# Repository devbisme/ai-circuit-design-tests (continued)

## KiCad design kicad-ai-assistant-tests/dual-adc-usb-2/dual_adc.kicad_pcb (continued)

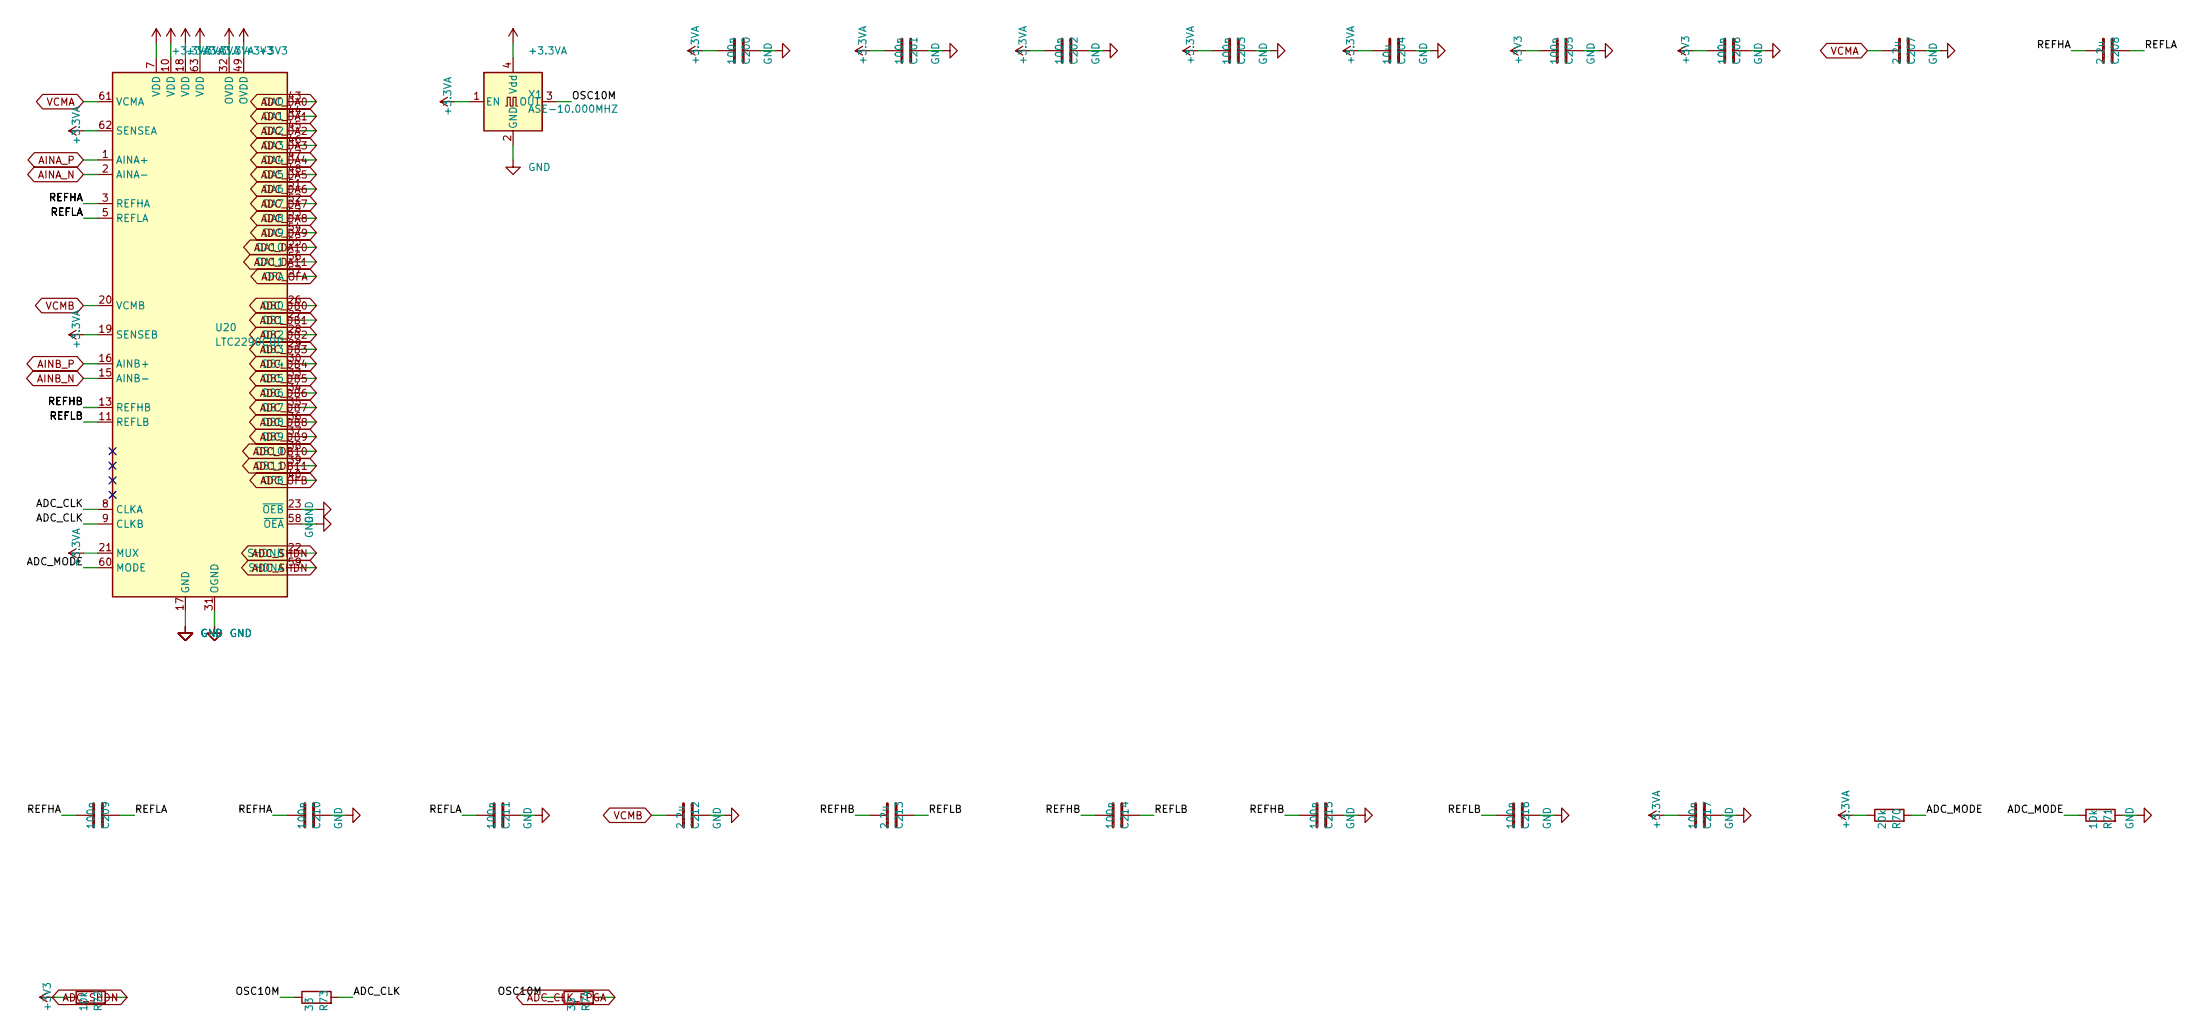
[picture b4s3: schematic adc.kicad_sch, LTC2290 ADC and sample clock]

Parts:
C200, C201, C202, C203, C205, C206, C209, C210, C211, C214, C215, C216, C217: 100n; C_0603_1608Metric
C204: 10u; C_0805_2012Metric
C207, C208, C212, C213: 2.2u; C_0603_1608Metric
R70: 20k; R_0603_1608Metric
R71, R72: 10k; R_0603_1608Metric
R73, R74: 33; R_0603_1608Metric
U20: LTC2290CUP; QFN-64-1EP_9x9mm_P0.5mm_EP7.15x7.15mm
X1: ASE-10.000MHZ; Oscillator_SMD_Abracon_ASE-4Pin_3.2x2.5mm

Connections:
+3.3VA: C200.1, C201.1, C202.1, C203.1, C204.1, C217.1, R70.1, U20.7 (VDD), U20.10 (VDD), U20.18 (VDD), U20.19 (SENSEB), U20.21 (MUX), U20.62 (SENSEA), U20.63 (VDD), X1.1 (EN), X1.4 (Vdd); also elsewhere on the board
+3V3: C205.1, C206.1, R72.1, U20.32 (OVDD), U20.49 (OVDD); also elsewhere on the board
/LTC2290 ADC and sample clock/ADC_CLK: R73.2, U20.8 (CLKA), U20.9 (CLKB)
/LTC2290 ADC and sample clock/ADC_MODE: R70.2, R71.1, U20.60 (MODE)
/LTC2290 ADC and sample clock/OSC10M: R73.1, R74.1, X1.3 (OUT)
/LTC2290 ADC and sample clock/REFHA: C208.1, C209.1, C210.1, U20.3 (REFHA), U20.4 (REFHA)
/LTC2290 ADC and sample clock/REFHB: C213.1, C214.1, C215.1, U20.13 (REFHB), U20.14 (REFHB)
/LTC2290 ADC and sample clock/REFLA: C208.2, C209.2, C211.1, U20.5 (REFLA), U20.6 (REFLA)
/LTC2290 ADC and sample clock/REFLB: C213.2, C214.2, C216.1, U20.11 (REFLB), U20.12 (REFLB)
ADC_CLK_FPGA: R74.2; also elsewhere on the board
ADC_DA0: U20.43 (DA0); also elsewhere on the board
ADC_DA1: U20.44 (DA1); also elsewhere on the board
ADC_DA2: U20.45 (DA2); also elsewhere on the board
ADC_DA3: U20.46 (DA3); also elsewhere on the board
ADC_DA4: U20.47 (DA4); also elsewhere on the board
ADC_DA5: U20.48 (DA5); also elsewhere on the board
ADC_DA6: U20.51 (DA6); also elsewhere on the board
ADC_DA7: U20.52 (DA7); also elsewhere on the board
ADC_DA8: U20.53 (DA8); also elsewhere on the board
ADC_DA9: U20.54 (DA9); also elsewhere on the board
ADC_DA10: U20.55 (DA10); also elsewhere on the board
ADC_DA11: U20.56 (DA11); also elsewhere on the board
ADC_DB0: U20.26 (DB0); also elsewhere on the board
ADC_DB1: U20.27 (DB1); also elsewhere on the board
ADC_DB2: U20.28 (DB2); also elsewhere on the board
ADC_DB3: U20.29 (DB3); also elsewhere on the board
ADC_DB4: U20.30 (DB4); also elsewhere on the board
ADC_DB5: U20.33 (DB5); also elsewhere on the board
ADC_DB6: U20.34 (DB6); also elsewhere on the board
ADC_DB7: U20.35 (DB7); also elsewhere on the board
ADC_DB8: U20.36 (DB8); also elsewhere on the board
ADC_DB9: U20.37 (DB9); also elsewhere on the board
ADC_DB10: U20.38 (DB10); also elsewhere on the board
ADC_DB11: U20.39 (DB11); also elsewhere on the board
ADC_OFA: U20.57 (OFA); also elsewhere on the board
ADC_OFB: U20.40 (OFB); also elsewhere on the board
ADC_SHDN: R72.2, U20.22 (SHDNB), U20.59 (SHDNA); also elsewhere on the board
AINA_N: U20.2 (AINA-); also elsewhere on the board
AINA_P: U20.1 (AINA+); also elsewhere on the board
AINB_N: U20.15 (AINB-); also elsewhere on the board
AINB_P: U20.16 (AINB+); also elsewhere on the board
GND: C200.2, C201.2, C202.2, C203.2, C204.2, C205.2, C206.2, C207.2, C210.2, C211.2, C212.2, C215.2, C216.2, C217.2, R71.2, U20.17 (GND), U20.23 (~OEB), U20.31 (OGND), U20.50 (OGND), U20.58 (~OEA), U20.64 (GND), U20.65 (GND), X1.2 (GND); also elsewhere on the board
VCMA: C207.1, U20.61 (VCMA); also elsewhere on the board
VCMB: C212.1, U20.20 (VCMB); also elsewhere on the board

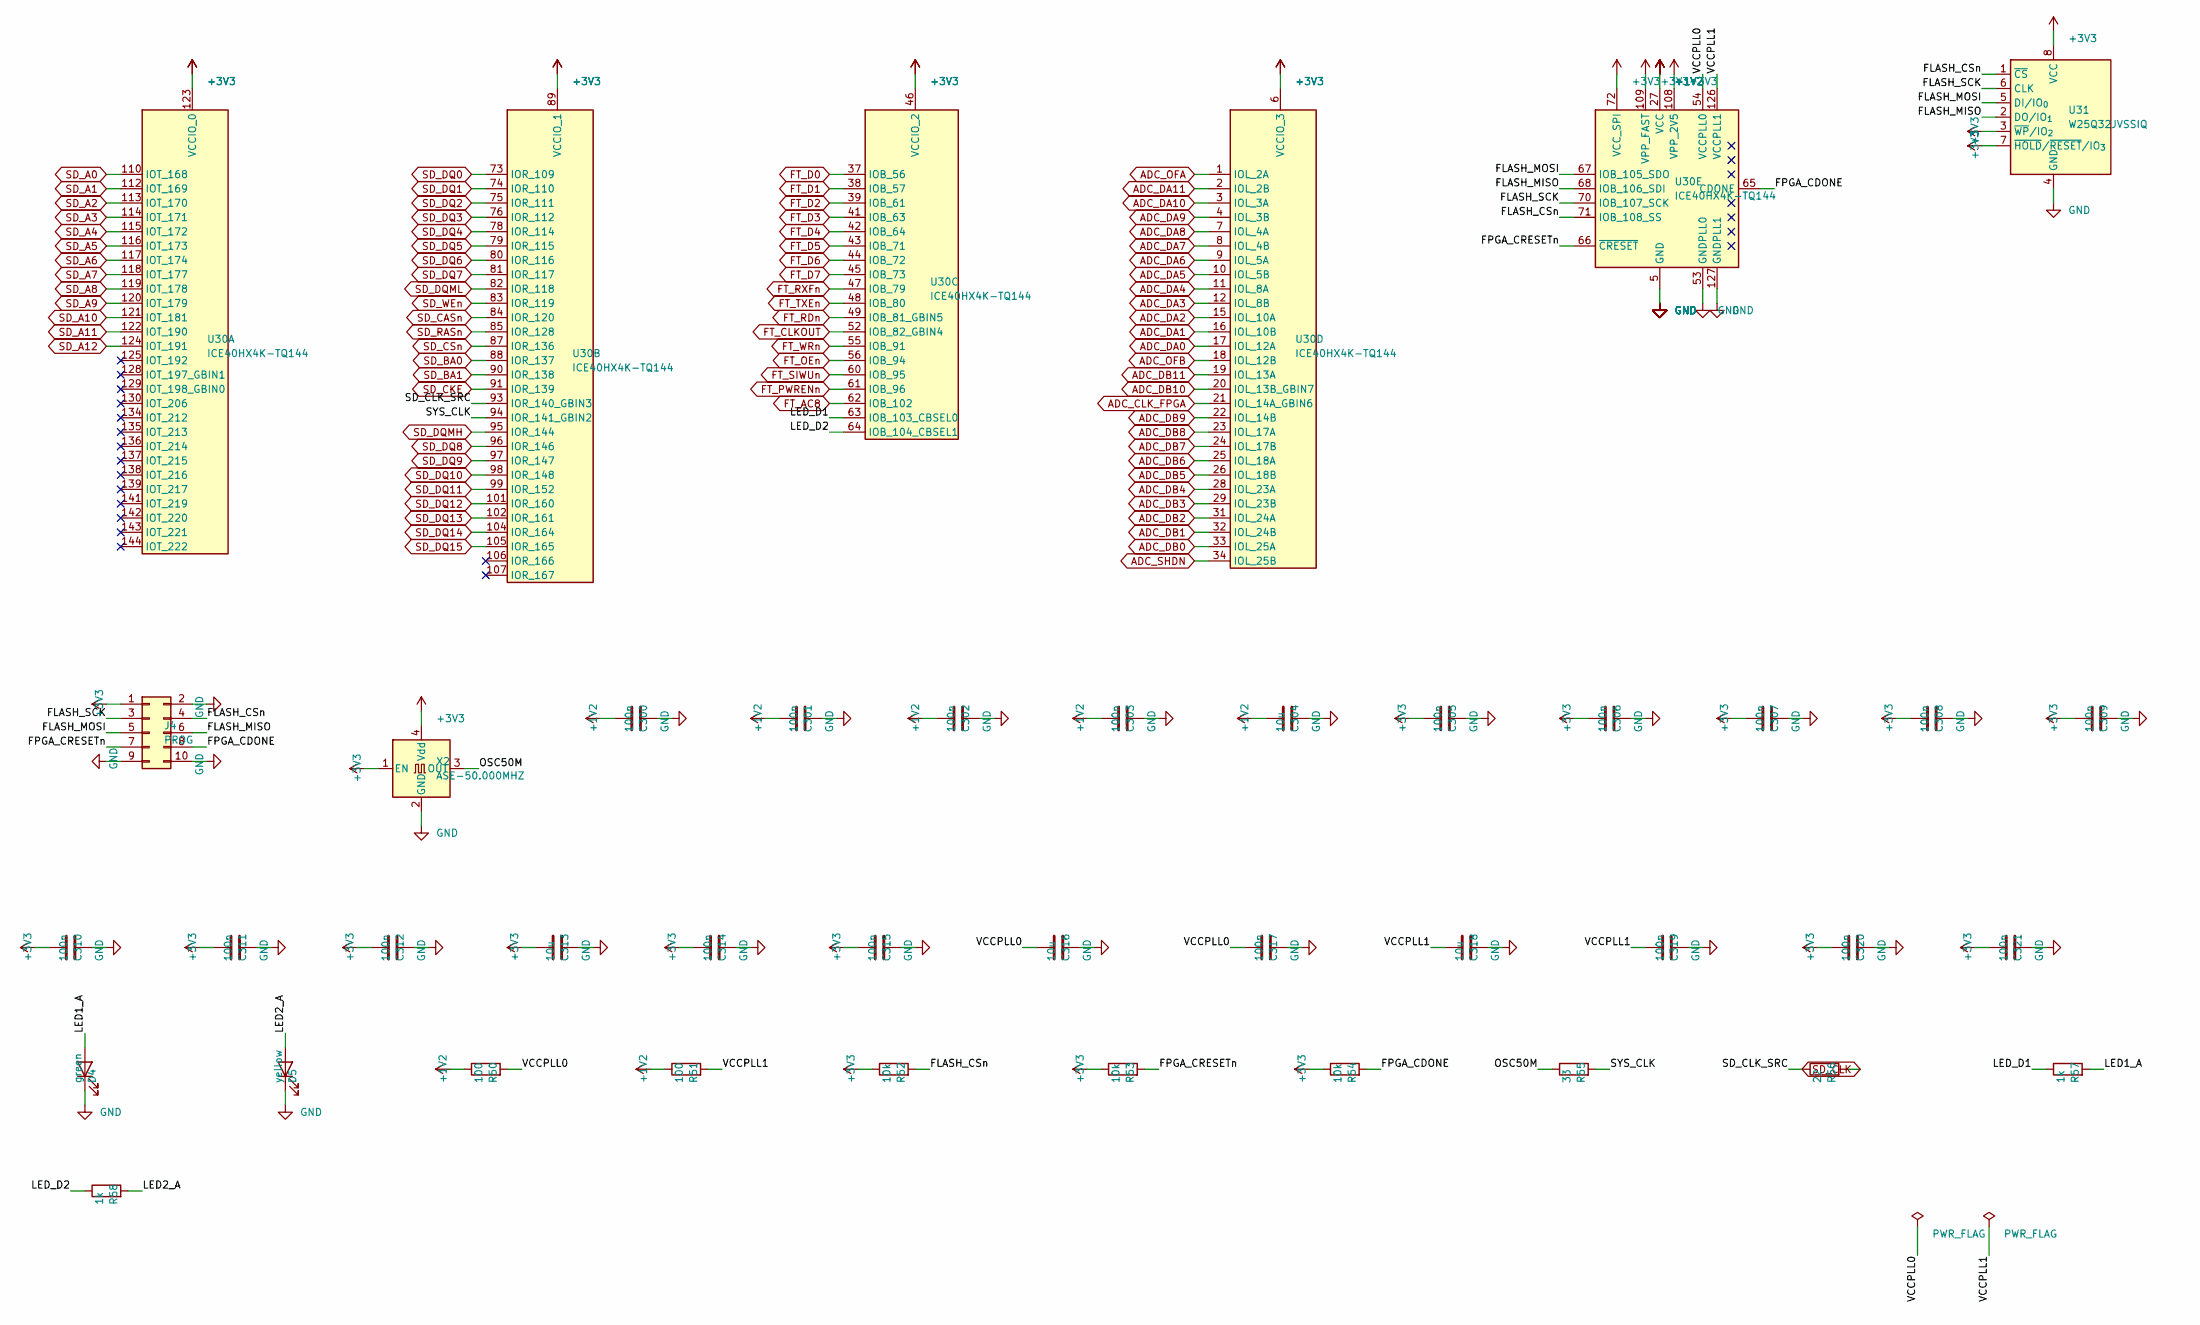
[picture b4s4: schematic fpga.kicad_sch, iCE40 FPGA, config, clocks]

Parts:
C300, C301, C302, C303, C305, C306, C307, C308, C309, C310, C311, C312, C314, C315, C317, C319, C320, C321: 100n; C_0603_1608Metric
C304, C313, C316, C318: 10u; C_0805_2012Metric
D4: green; LED_0603_1608Metric
D5: yellow; LED_0603_1608Metric
J4: PROG; PinHeader_2x05_P2.54mm_Vertical
R50, R51: 100; R_0603_1608Metric
R52, R53, R54: 10k; R_0603_1608Metric
R55: 33; R_0603_1608Metric
R56: 22; R_0603_1608Metric
R57, R58: 1k; R_0603_1608Metric
U30: ICE40HX4K-TQ144; TQFP-144_20x20mm_P0.5mm
U31: W25Q32JVSSIQ; SOIC-8_5.3x5.3mm_P1.27mm
X2: ASE-50.000MHZ; Oscillator_SMD_Abracon_ASE-4Pin_3.2x2.5mm

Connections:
+1V2: C300.1, C301.1, C302.1, C303.1, C304.1, R50.1, R51.1, U30.27 (VCC), U30.40 (VCC), U30.92 (VCC), U30.111 (VCC); also elsewhere on the board
+3V3: C305.1, C306.1, C307.1, C308.1, C309.1, C310.1, C311.1, C312.1, C313.1, C314.1, C315.1, C320.1, C321.1, J4.1, R52.1, R53.1, R54.1, U30.6 (VCCIO_3), U30.30 (VCCIO_3), U30.46 (VCCIO_2), U30.57 (VCCIO_2), U30.72 (VCC_SPI), U30.89 (VCCIO_1), U30.100 (VCCIO_1), U30.108 (VPP_2V5), U30.109 (VPP_FAST), U30.123 (VCCIO_0), U30.131 (VCCIO_0), U31.3 (~WP/IO_{2}), U31.7 (~HOLD/~RESET/IO_{3}), U31.8 (VCC), X2.1 (EN), X2.4 (Vdd); also elsewhere on the board
/iCE40 FPGA, config, clocks/FLASH_CSn: J4.4, R52.2, U30.71 (IOB_108_SS), U31.1 (~CS)
/iCE40 FPGA, config, clocks/FLASH_MISO: J4.6, U30.68 (IOB_106_SDI), U31.2 (DO/IO_{1})
/iCE40 FPGA, config, clocks/FLASH_MOSI: J4.5, U30.67 (IOB_105_SDO), U31.5 (DI/IO_{0})
/iCE40 FPGA, config, clocks/FLASH_SCK: J4.3, U30.70 (IOB_107_SCK), U31.6 (CLK)
/iCE40 FPGA, config, clocks/FPGA_CDONE: J4.8, R54.2, U30.65 (CDONE)
/iCE40 FPGA, config, clocks/FPGA_CRESETn: J4.7, R53.2, U30.66 (~CRESET)
/iCE40 FPGA, config, clocks/LED1_A: D4.2 (A), R57.2
/iCE40 FPGA, config, clocks/LED2_A: D5.2 (A), R58.2
/iCE40 FPGA, config, clocks/LED_D1: R57.1, U30.63 (IOB_103_CBSEL0)
/iCE40 FPGA, config, clocks/LED_D2: R58.1, U30.64 (IOB_104_CBSEL1)
/iCE40 FPGA, config, clocks/OSC50M: R55.1, X2.3 (OUT)
/iCE40 FPGA, config, clocks/SD_CLK_SRC: R56.1, U30.93 (IOR_140_GBIN3)
/iCE40 FPGA, config, clocks/SYS_CLK: R55.2, U30.94 (IOR_141_GBIN2)
/iCE40 FPGA, config, clocks/VCCPLL0: C316.1, C317.1, R50.2, U30.54 (VCCPLL0)
/iCE40 FPGA, config, clocks/VCCPLL1: C318.1, C319.1, R51.2, U30.126 (VCCPLL1)
ADC_CLK_FPGA: U30.21 (IOL_14A_GBIN6); also elsewhere on the board
ADC_DA0: U30.17 (IOL_12A); also elsewhere on the board
ADC_DA1: U30.16 (IOL_10B); also elsewhere on the board
ADC_DA2: U30.15 (IOL_10A); also elsewhere on the board
ADC_DA3: U30.12 (IOL_8B); also elsewhere on the board
ADC_DA4: U30.11 (IOL_8A); also elsewhere on the board
ADC_DA5: U30.10 (IOL_5B); also elsewhere on the board
ADC_DA6: U30.9 (IOL_5A); also elsewhere on the board
ADC_DA7: U30.8 (IOL_4B); also elsewhere on the board
ADC_DA8: U30.7 (IOL_4A); also elsewhere on the board
ADC_DA9: U30.4 (IOL_3B); also elsewhere on the board
ADC_DA10: U30.3 (IOL_3A); also elsewhere on the board
ADC_DA11: U30.2 (IOL_2B); also elsewhere on the board
ADC_DB0: U30.33 (IOL_25A); also elsewhere on the board
ADC_DB1: U30.32 (IOL_24B); also elsewhere on the board
ADC_DB2: U30.31 (IOL_24A); also elsewhere on the board
ADC_DB3: U30.29 (IOL_23B); also elsewhere on the board
ADC_DB4: U30.28 (IOL_23A); also elsewhere on the board
ADC_DB5: U30.26 (IOL_18B); also elsewhere on the board
ADC_DB6: U30.25 (IOL_18A); also elsewhere on the board
ADC_DB7: U30.24 (IOL_17B); also elsewhere on the board
ADC_DB8: U30.23 (IOL_17A); also elsewhere on the board
ADC_DB9: U30.22 (IOL_14B); also elsewhere on the board
ADC_DB10: U30.20 (IOL_13B_GBIN7); also elsewhere on the board
ADC_DB11: U30.19 (IOL_13A); also elsewhere on the board
ADC_OFA: U30.1 (IOL_2A); also elsewhere on the board
ADC_OFB: U30.18 (IOL_12B); also elsewhere on the board
ADC_SHDN: U30.34 (IOL_25B); also elsewhere on the board
FT_AC8: U30.62 (IOB_102); also elsewhere on the board
FT_CLKOUT: U30.52 (IOB_82_GBIN4); also elsewhere on the board
FT_D0: U30.37 (IOB_56); also elsewhere on the board
FT_D1: U30.38 (IOB_57); also elsewhere on the board
FT_D2: U30.39 (IOB_61); also elsewhere on the board
FT_D3: U30.41 (IOB_63); also elsewhere on the board
FT_D4: U30.42 (IOB_64); also elsewhere on the board
FT_D5: U30.43 (IOB_71); also elsewhere on the board
FT_D6: U30.44 (IOB_72); also elsewhere on the board
FT_D7: U30.45 (IOB_73); also elsewhere on the board
FT_OEn: U30.56 (IOB_94); also elsewhere on the board
FT_PWRENn: U30.61 (IOB_96); also elsewhere on the board
FT_RDn: U30.49 (IOB_81_GBIN5); also elsewhere on the board
FT_RXFn: U30.47 (IOB_79); also elsewhere on the board
FT_SIWUn: U30.60 (IOB_95); also elsewhere on the board
FT_TXEn: U30.48 (IOB_80); also elsewhere on the board
FT_WRn: U30.55 (IOB_91); also elsewhere on the board
GND: C300.2, C301.2, C302.2, C303.2, C304.2, C305.2, C306.2, C307.2, C308.2, C309.2, C310.2, C311.2, C312.2, C313.2, C314.2, C315.2, C316.2, C317.2, C318.2, C319.2, C320.2, C321.2, D4.1 (K), D5.1 (K), J4.2, J4.9, J4.10, U30.5 (GND), U30.13 (GND), U30.14 (GND), U30.53 (GNDPLL0), U30.59 (GND), U30.69 (GND), U30.86 (GND), U30.103 (GND), U30.127 (GNDPLL1), U30.132 (GND), U30.140 (GND), U31.4 (GND), X2.2 (GND); also elsewhere on the board
SD_A0: U30.110 (IOT_168); also elsewhere on the board
SD_A1: U30.112 (IOT_169); also elsewhere on the board
SD_A2: U30.113 (IOT_170); also elsewhere on the board
SD_A3: U30.114 (IOT_171); also elsewhere on the board
SD_A4: U30.115 (IOT_172); also elsewhere on the board
SD_A5: U30.116 (IOT_173); also elsewhere on the board
SD_A6: U30.117 (IOT_174); also elsewhere on the board
SD_A7: U30.118 (IOT_177); also elsewhere on the board
SD_A8: U30.119 (IOT_178); also elsewhere on the board
SD_A9: U30.120 (IOT_179); also elsewhere on the board
SD_A10: U30.121 (IOT_181); also elsewhere on the board
SD_A11: U30.122 (IOT_190); also elsewhere on the board
SD_A12: U30.124 (IOT_191); also elsewhere on the board
SD_BA0: U30.88 (IOR_137); also elsewhere on the board
SD_BA1: U30.90 (IOR_138); also elsewhere on the board
SD_CASn: U30.84 (IOR_120); also elsewhere on the board
SD_CKE: U30.91 (IOR_139); also elsewhere on the board
SD_CLK: R56.2; also elsewhere on the board
SD_CSn: U30.87 (IOR_136); also elsewhere on the board
SD_DQ0: U30.73 (IOR_109); also elsewhere on the board
SD_DQ1: U30.74 (IOR_110); also elsewhere on the board
SD_DQ2: U30.75 (IOR_111); also elsewhere on the board
SD_DQ3: U30.76 (IOR_112); also elsewhere on the board
SD_DQ4: U30.78 (IOR_114); also elsewhere on the board
SD_DQ5: U30.79 (IOR_115); also elsewhere on the board
SD_DQ6: U30.80 (IOR_116); also elsewhere on the board
SD_DQ7: U30.81 (IOR_117); also elsewhere on the board
SD_DQ8: U30.96 (IOR_146); also elsewhere on the board
SD_DQ9: U30.97 (IOR_147); also elsewhere on the board
SD_DQ10: U30.98 (IOR_148); also elsewhere on the board
SD_DQ11: U30.99 (IOR_152); also elsewhere on the board
SD_DQ12: U30.101 (IOR_160); also elsewhere on the board
SD_DQ13: U30.102 (IOR_161); also elsewhere on the board
SD_DQ14: U30.104 (IOR_164); also elsewhere on the board
SD_DQ15: U30.105 (IOR_165); also elsewhere on the board
SD_DQMH: U30.95 (IOR_144); also elsewhere on the board
SD_DQML: U30.82 (IOR_118); also elsewhere on the board
SD_RASn: U30.85 (IOR_128); also elsewhere on the board
SD_WEn: U30.83 (IOR_119); also elsewhere on the board

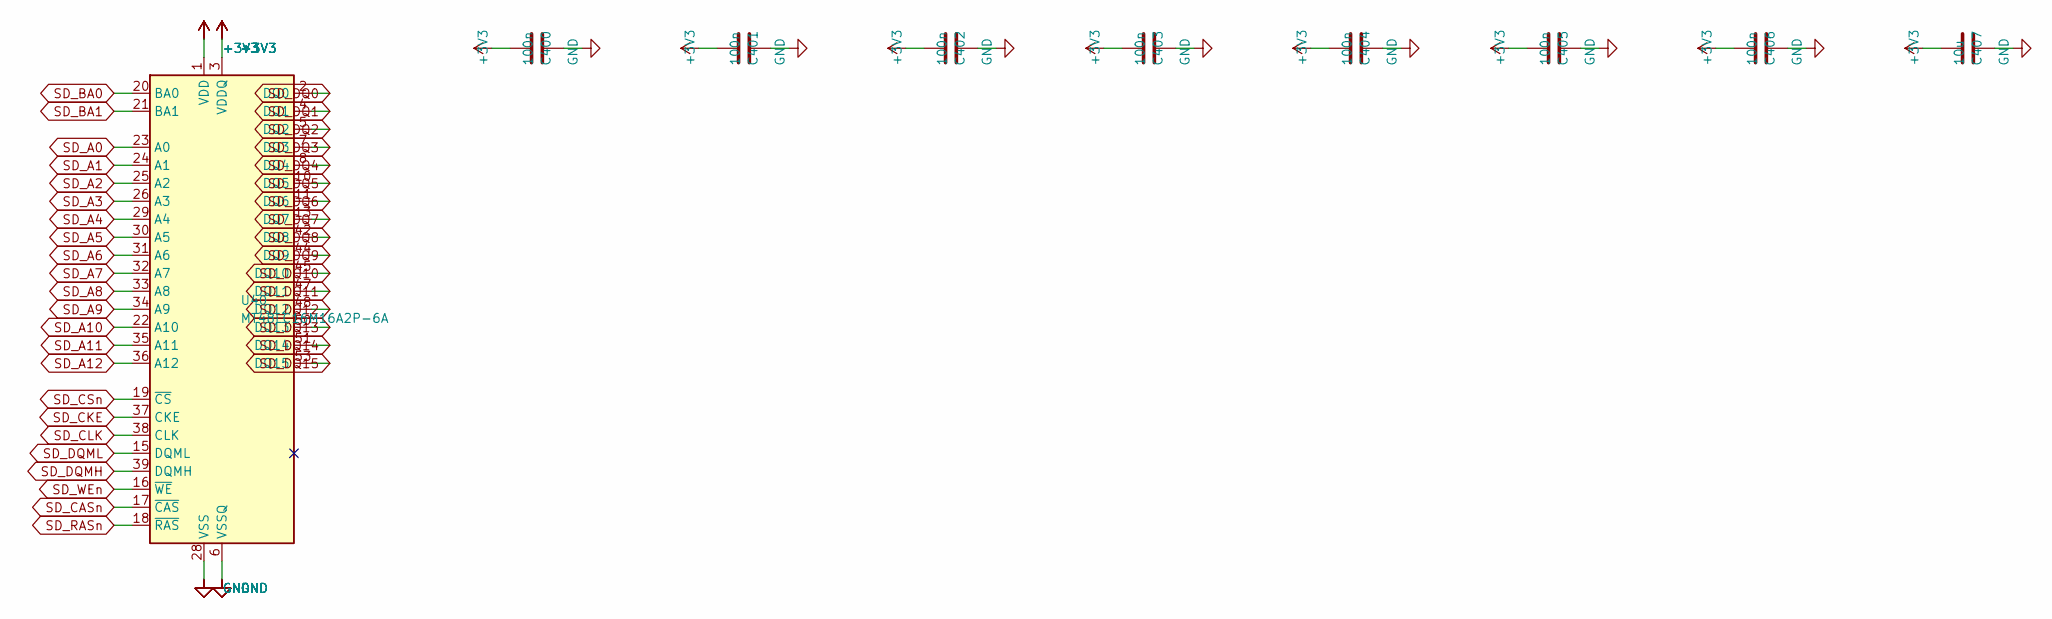
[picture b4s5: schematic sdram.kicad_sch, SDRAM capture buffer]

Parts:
C400, C401, C402, C403, C404, C405, C406: 100n; C_0603_1608Metric
C407: 10u; C_0805_2012Metric
U40: MT48LC16M16A2P-6A; TSOP-II-54_22.2x10.16mm_P0.8mm

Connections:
+3V3: C400.1, C401.1, C402.1, C403.1, C404.1, C405.1, C406.1, C407.1, U40.1 (VDD), U40.3 (VDDQ), U40.9 (VDDQ), U40.14 (VDD), U40.27 (VDD), U40.43 (VDDQ), U40.49 (VDDQ); also elsewhere on the board
GND: C400.2, C401.2, C402.2, C403.2, C404.2, C405.2, C406.2, C407.2, U40.6 (VSSQ), U40.12 (VSSQ), U40.28 (VSS), U40.41 (VSS), U40.46 (VSSQ), U40.52 (VSSQ), U40.54 (VSS); also elsewhere on the board
SD_A0: U40.23 (A0); also elsewhere on the board
SD_A1: U40.24 (A1); also elsewhere on the board
SD_A2: U40.25 (A2); also elsewhere on the board
SD_A3: U40.26 (A3); also elsewhere on the board
SD_A4: U40.29 (A4); also elsewhere on the board
SD_A5: U40.30 (A5); also elsewhere on the board
SD_A6: U40.31 (A6); also elsewhere on the board
SD_A7: U40.32 (A7); also elsewhere on the board
SD_A8: U40.33 (A8); also elsewhere on the board
SD_A9: U40.34 (A9); also elsewhere on the board
SD_A10: U40.22 (A10); also elsewhere on the board
SD_A11: U40.35 (A11); also elsewhere on the board
SD_A12: U40.36 (A12); also elsewhere on the board
SD_BA0: U40.20 (BA0); also elsewhere on the board
SD_BA1: U40.21 (BA1); also elsewhere on the board
SD_CASn: U40.17 (~CAS); also elsewhere on the board
SD_CKE: U40.37 (CKE); also elsewhere on the board
SD_CLK: U40.38 (CLK); also elsewhere on the board
SD_CSn: U40.19 (~CS); also elsewhere on the board
SD_DQ0: U40.2 (DQ0); also elsewhere on the board
SD_DQ1: U40.4 (DQ1); also elsewhere on the board
SD_DQ2: U40.5 (DQ2); also elsewhere on the board
SD_DQ3: U40.7 (DQ3); also elsewhere on the board
SD_DQ4: U40.8 (DQ4); also elsewhere on the board
SD_DQ5: U40.10 (DQ5); also elsewhere on the board
SD_DQ6: U40.11 (DQ6); also elsewhere on the board
SD_DQ7: U40.13 (DQ7); also elsewhere on the board
SD_DQ8: U40.42 (DQ8); also elsewhere on the board
SD_DQ9: U40.44 (DQ9); also elsewhere on the board
SD_DQ10: U40.45 (DQ10); also elsewhere on the board
SD_DQ11: U40.47 (DQ11); also elsewhere on the board
SD_DQ12: U40.48 (DQ12); also elsewhere on the board
SD_DQ13: U40.50 (DQ13); also elsewhere on the board
SD_DQ14: U40.51 (DQ14); also elsewhere on the board
SD_DQ15: U40.53 (DQ15); also elsewhere on the board
SD_DQMH: U40.39 (DQMH); also elsewhere on the board
SD_DQML: U40.15 (DQML); also elsewhere on the board
SD_RASn: U40.18 (~RAS); also elsewhere on the board
SD_WEn: U40.16 (~WE); also elsewhere on the board

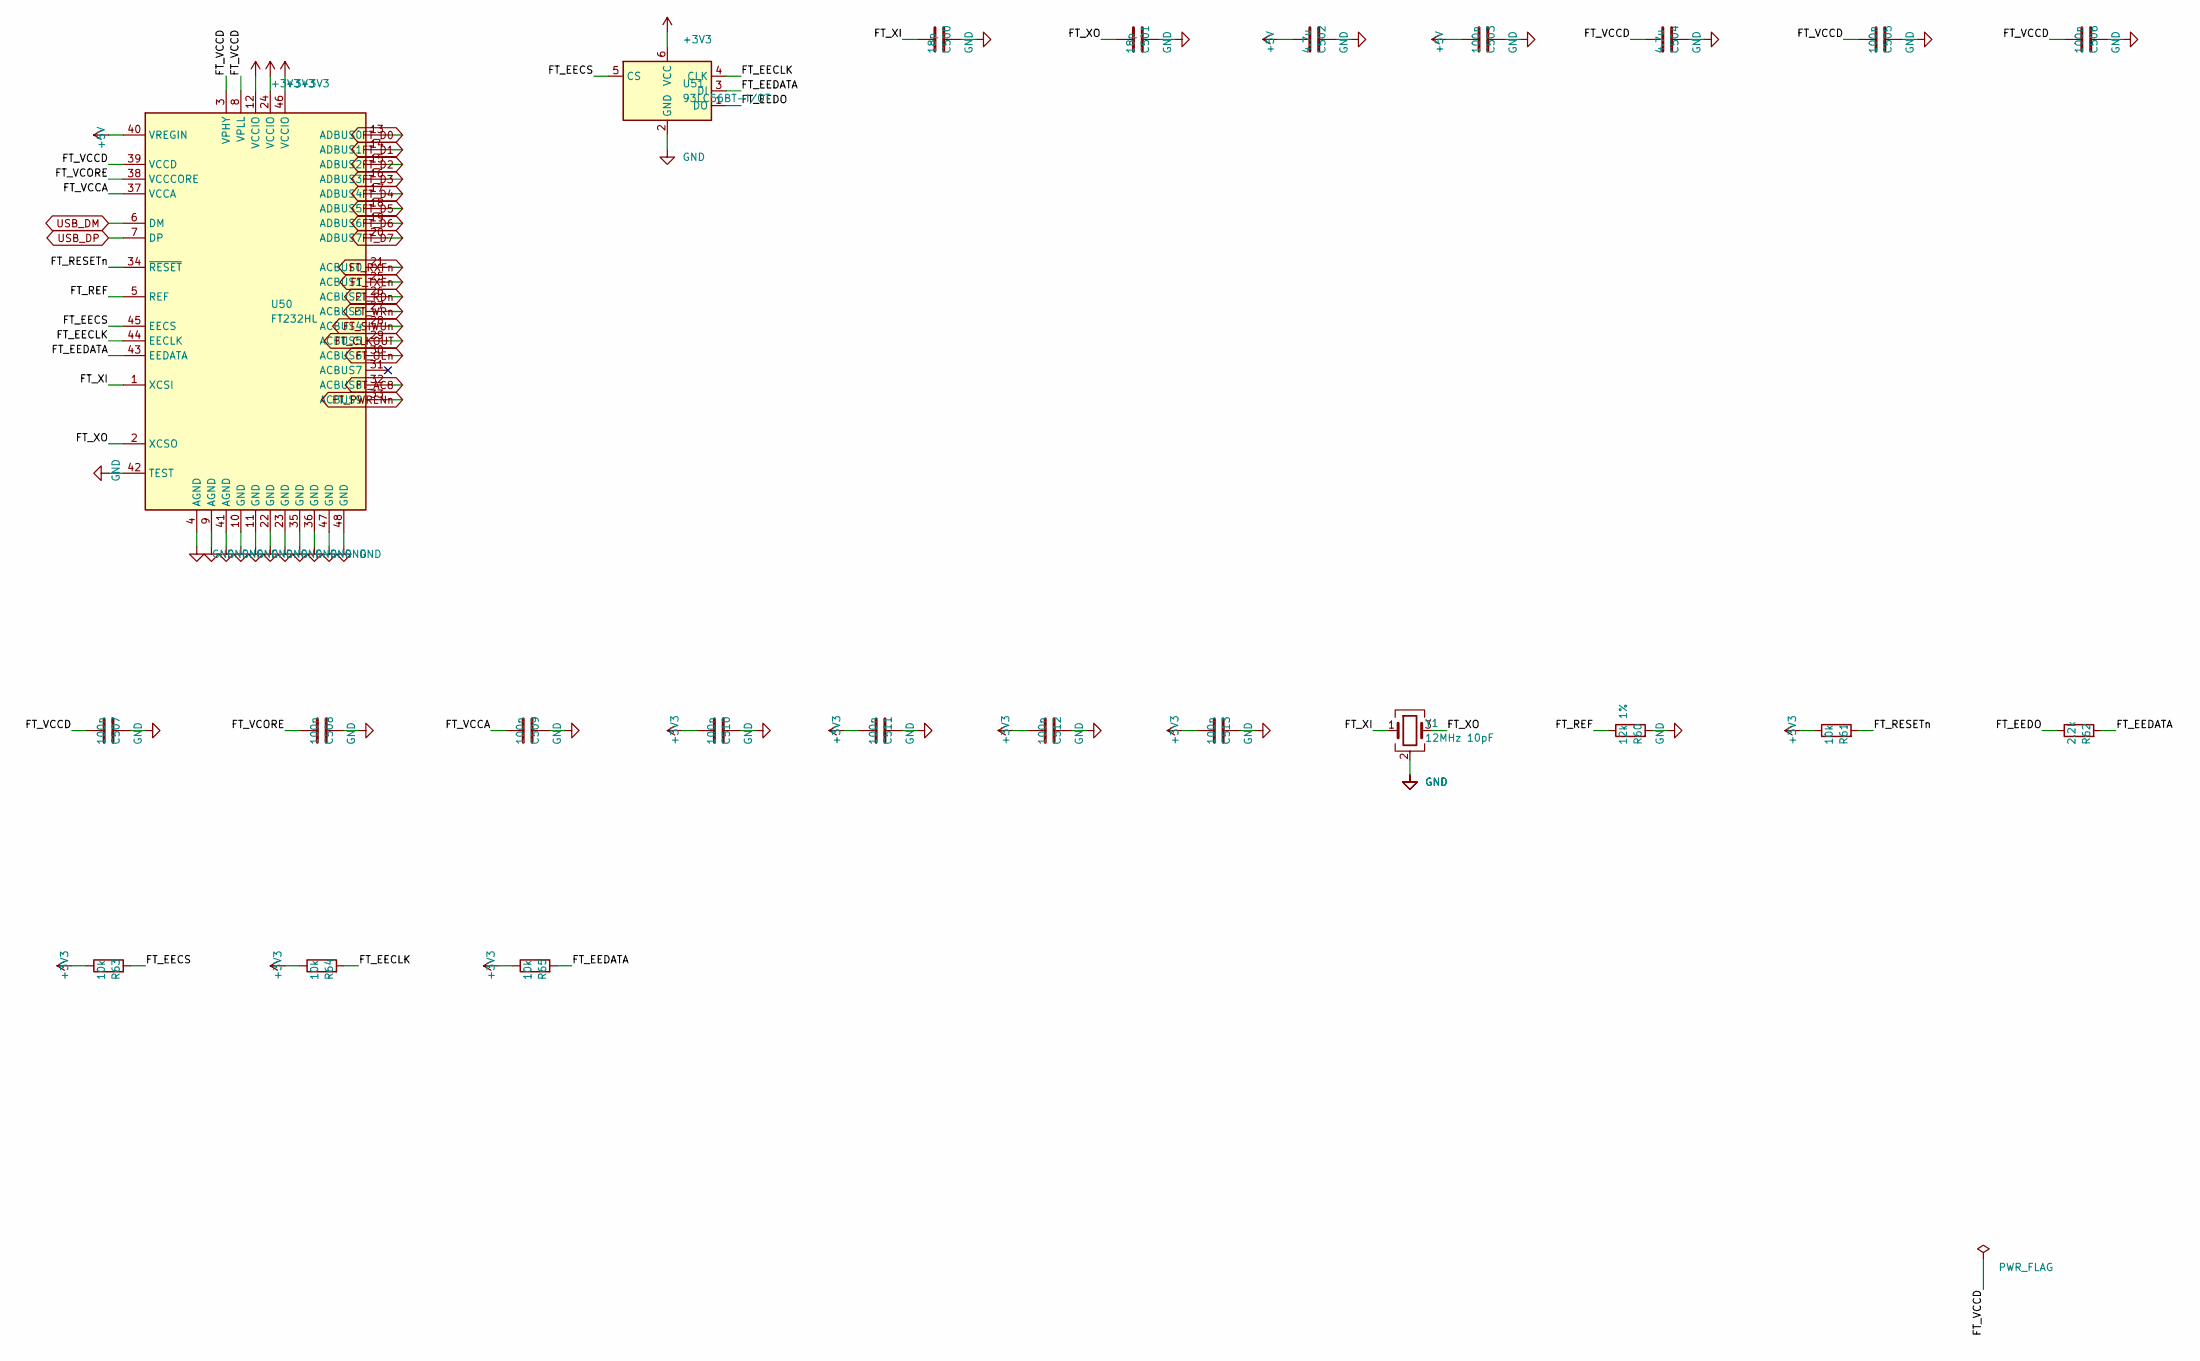
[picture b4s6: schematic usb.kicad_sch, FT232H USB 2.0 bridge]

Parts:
C500, C501: 18p; C_0603_1608Metric
C502, C504: 4.7u; C_0805_2012Metric
C503, C505, C506, C507, C508, C509, C510, C511, C512, C513: 100n; C_0603_1608Metric
R60: 12k 1%; R_0603_1608Metric
R61, R63, R64, R65: 10k; R_0603_1608Metric
R62: 2.2k; R_0603_1608Metric
U50: FT232HL; LQFP-48_7x7mm_P0.5mm
U51: 93LC56BT-I/OT; SOT-23-6
Y1: 12MHz 10pF; Crystal_SMD_3225-4Pin_3.2x2.5mm

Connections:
+3V3: C510.1, C511.1, C512.1, C513.1, R61.1, R63.1, R64.1, R65.1, U50.12 (VCCIO), U50.24 (VCCIO), U50.46 (VCCIO), U51.6 (VCC); also elsewhere on the board
+5V: C502.1, C503.1, U50.40 (VREGIN); also elsewhere on the board
/FT232H USB 2.0 bridge/FT_EECLK: R64.2, U50.44 (EECLK), U51.4 (CLK)
/FT232H USB 2.0 bridge/FT_EECS: R63.2, U50.45 (EECS), U51.5 (CS)
/FT232H USB 2.0 bridge/FT_EEDATA: R62.2, R65.2, U50.43 (EEDATA), U51.3 (DI)
/FT232H USB 2.0 bridge/FT_EEDO: R62.1, U51.1 (DO)
/FT232H USB 2.0 bridge/FT_REF: R60.1, U50.5 (REF)
/FT232H USB 2.0 bridge/FT_RESETn: R61.2, U50.34 (~RESET)
/FT232H USB 2.0 bridge/FT_VCCA: C509.1, U50.37 (VCCA)
/FT232H USB 2.0 bridge/FT_VCCD: C504.1, C505.1, C506.1, C507.1, U50.3 (VPHY), U50.8 (VPLL), U50.39 (VCCD)
/FT232H USB 2.0 bridge/FT_VCORE: C508.1, U50.38 (VCCCORE)
/FT232H USB 2.0 bridge/FT_XI: C500.1, U50.1 (XCSI), Y1.1
/FT232H USB 2.0 bridge/FT_XO: C501.1, U50.2 (XCSO), Y1.3
FT_AC8: U50.32 (ACBUS8); also elsewhere on the board
FT_CLKOUT: U50.29 (ACBUS5); also elsewhere on the board
FT_D0: U50.13 (ADBUS0); also elsewhere on the board
FT_D1: U50.14 (ADBUS1); also elsewhere on the board
FT_D2: U50.15 (ADBUS2); also elsewhere on the board
FT_D3: U50.16 (ADBUS3); also elsewhere on the board
FT_D4: U50.17 (ADBUS4); also elsewhere on the board
FT_D5: U50.18 (ADBUS5); also elsewhere on the board
FT_D6: U50.19 (ADBUS6); also elsewhere on the board
FT_D7: U50.20 (ADBUS7); also elsewhere on the board
FT_OEn: U50.30 (ACBUS6); also elsewhere on the board
FT_PWRENn: U50.33 (ACBUS9); also elsewhere on the board
FT_RDn: U50.26 (ACBUS2); also elsewhere on the board
FT_RXFn: U50.21 (ACBUS0); also elsewhere on the board
FT_SIWUn: U50.28 (ACBUS4); also elsewhere on the board
FT_TXEn: U50.25 (ACBUS1); also elsewhere on the board
FT_WRn: U50.27 (ACBUS3); also elsewhere on the board
GND: C500.2, C501.2, C502.2, C503.2, C504.2, C505.2, C506.2, C507.2, C508.2, C509.2, C510.2, C511.2, C512.2, C513.2, R60.2, U50.4 (AGND), U50.9 (AGND), U50.10 (GND), U50.11 (GND), U50.22 (GND), U50.23 (GND), U50.35 (GND), U50.36 (GND), U50.41 (AGND), U50.42 (TEST), U50.47 (GND), U50.48 (GND), U51.2 (GND), Y1.2 (G), Y1.4 (G); also elsewhere on the board
USB_DM: U50.6 (DM); also elsewhere on the board
USB_DP: U50.7 (DP); also elsewhere on the board
